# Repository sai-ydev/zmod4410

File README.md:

# zmod4410
 Renesas ZMOD4410 sensor

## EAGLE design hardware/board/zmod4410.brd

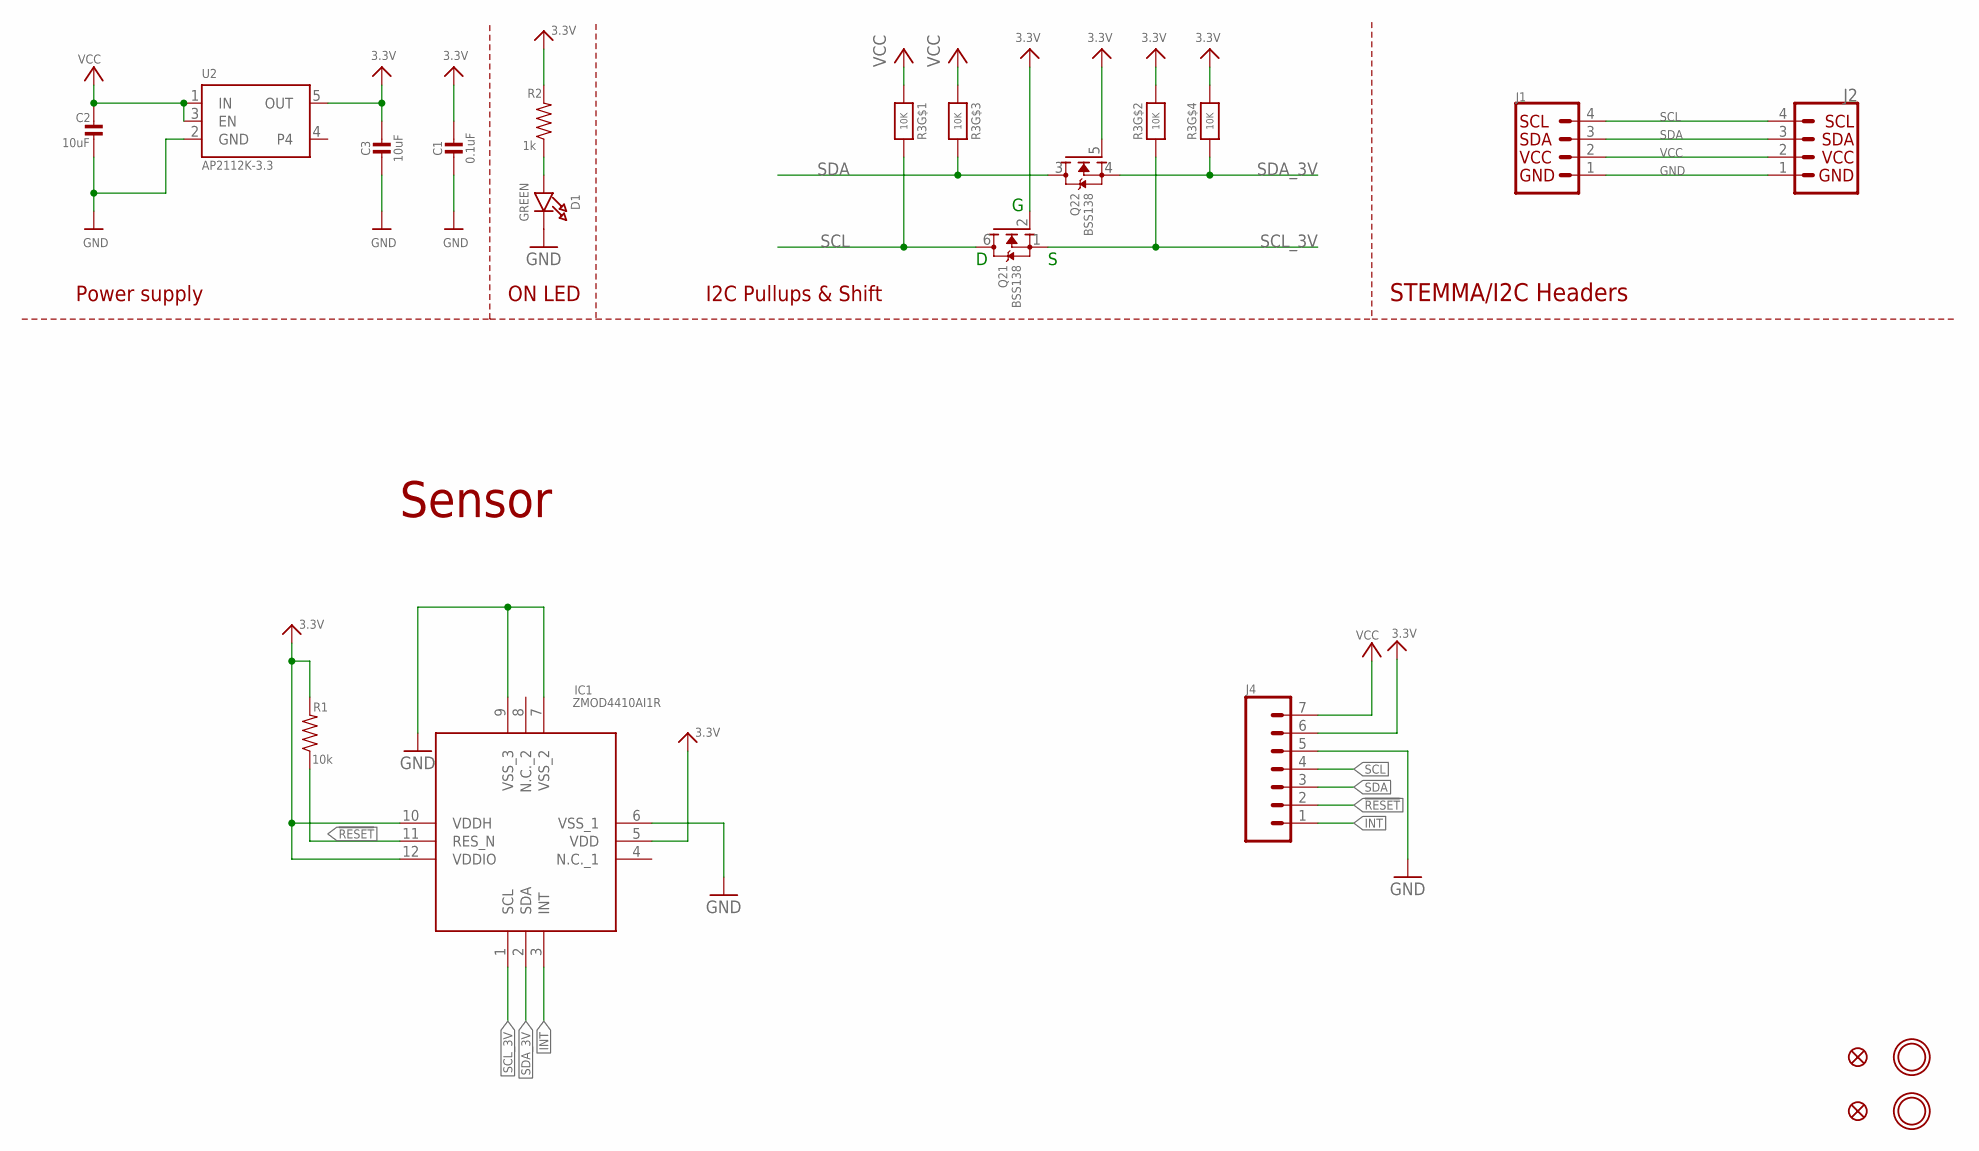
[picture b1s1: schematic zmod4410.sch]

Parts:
C1: 0.1uF; 0603-NO
C2, C3: 10uF; 0805-NO
D1: GREEN; CHIPLED_0603_NOOUTLINE
FID3, FID4: FIDUCIAL_1MM
GND: MOUNTINGHOLE2.5; MOUNTINGHOLE_2.5_PLATED
IC1: ZMOD4410AI1R
J1, J2: QWIIC_CONNECTORJS-1MM; 1X04_1MM_RA
J4: CONN_07; 1X07
Q2: BSS138; SOT363
R1: 10k; 0603
R2: 1k; 0603
R3: 10K; RESPACK_4X0603
U2: AP2112K-3.3; SOT23-5
U$8: MOUNTINGHOLE2.5; MOUNTINGHOLE_2.5_PLATED

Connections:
3.3V: C1.1, C3.1, IC1.5 (VDD), IC1.10 (VDDH), IC1.12 (VDDIO), J4.6, Q2.2 (G), Q2.5 (G), R1.2, R2.2, R3.2 (1), R3.4 (1), U2.5 (OUT)
!RESET: IC1.11 (RES_N), J4.2, R1.1
GND: C1.2, C2.2, C3.2, D1.C, IC1.6 (VSS_1), IC1.7 (VSS_2), IC1.9 (VSS_3), J1.1, J2.1, J4.5, U2.2 (GND)
INT: IC1.3 (INT), J4.1
unnamed: D1.A, R2.1
SCL: J1.4, J2.4, J4.4, Q2.6 (D), R3.8 (2)
SCL_3V: IC1.1 (SCL), Q2.1 (S), R3.7 (2)
SDA: J1.3, J2.3, J4.3, Q2.3 (D), R3.6 (2)
SDA_3V: IC1.2 (SDA), Q2.4 (S), R3.5 (2)
VCC: C2.1, J1.2, J2.2, J4.7, R3.1, R3.3 (1), U2.1 (IN), U2.3 (EN)

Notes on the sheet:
Power supply
ON LED
I2C Pullups & Shift
STEMMA/I2C Headers
Sensor

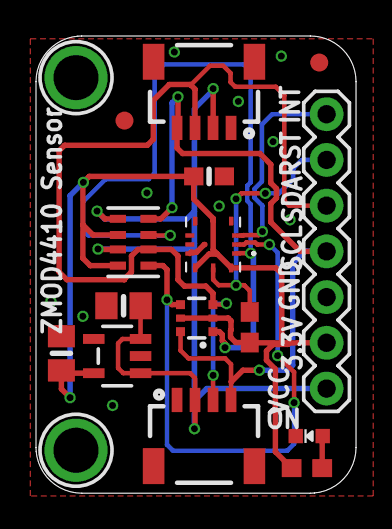
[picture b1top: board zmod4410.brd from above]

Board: 2 copper layers, 17.8 x 25.4 mm, 17 parts (0 on the bottom side), 10 nets.

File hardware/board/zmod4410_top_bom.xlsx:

Comment | Designator | Footprint | LCSC Part #
Qwiic | J1 J2 | JST-1mm | C160404
0.1uF | C1 | 0603-NO | C141382
1k | R2 | 603 | C3015791
10K | R3 | RESPACK_4X0603 | C153137
10k | R1 | 603 | C3015825
10uF | C2 C3 | 0805-NO | C2835556
AP2112K-3.3 | U2 | SOT23-5 | C51118
BSS138 | Q2 | SOT363 | C154900
GREEN | D1 | CHIPLED_0603_NOOUTLINE | C130724
ZMOD4410AI1R | IC1 | ZMOD4410AI1R | ZMOD4410AI1R

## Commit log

2023-05-15 Completed design files
2023-05-15 Modification to package

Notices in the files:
parts and their libraries:
microbuilder: This work is placed in the public domain, and may be freely used for commercial and non-commercial work with the following conditions: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
SparkFun-Connectors: Licensing: Creative Commons ShareAlike 4.0 International - https://creativecommons.org/licenses/by-sa/4.0
